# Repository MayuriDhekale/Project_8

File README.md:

# Project_8
<br>
<b><h2>Compact Li-Ion Charger & Microcontroller Board</h2></b>
<br>
Designed a custom circular 2-layer PCB to handle Li-Ion charging and audio alerts in a really compact form factor.

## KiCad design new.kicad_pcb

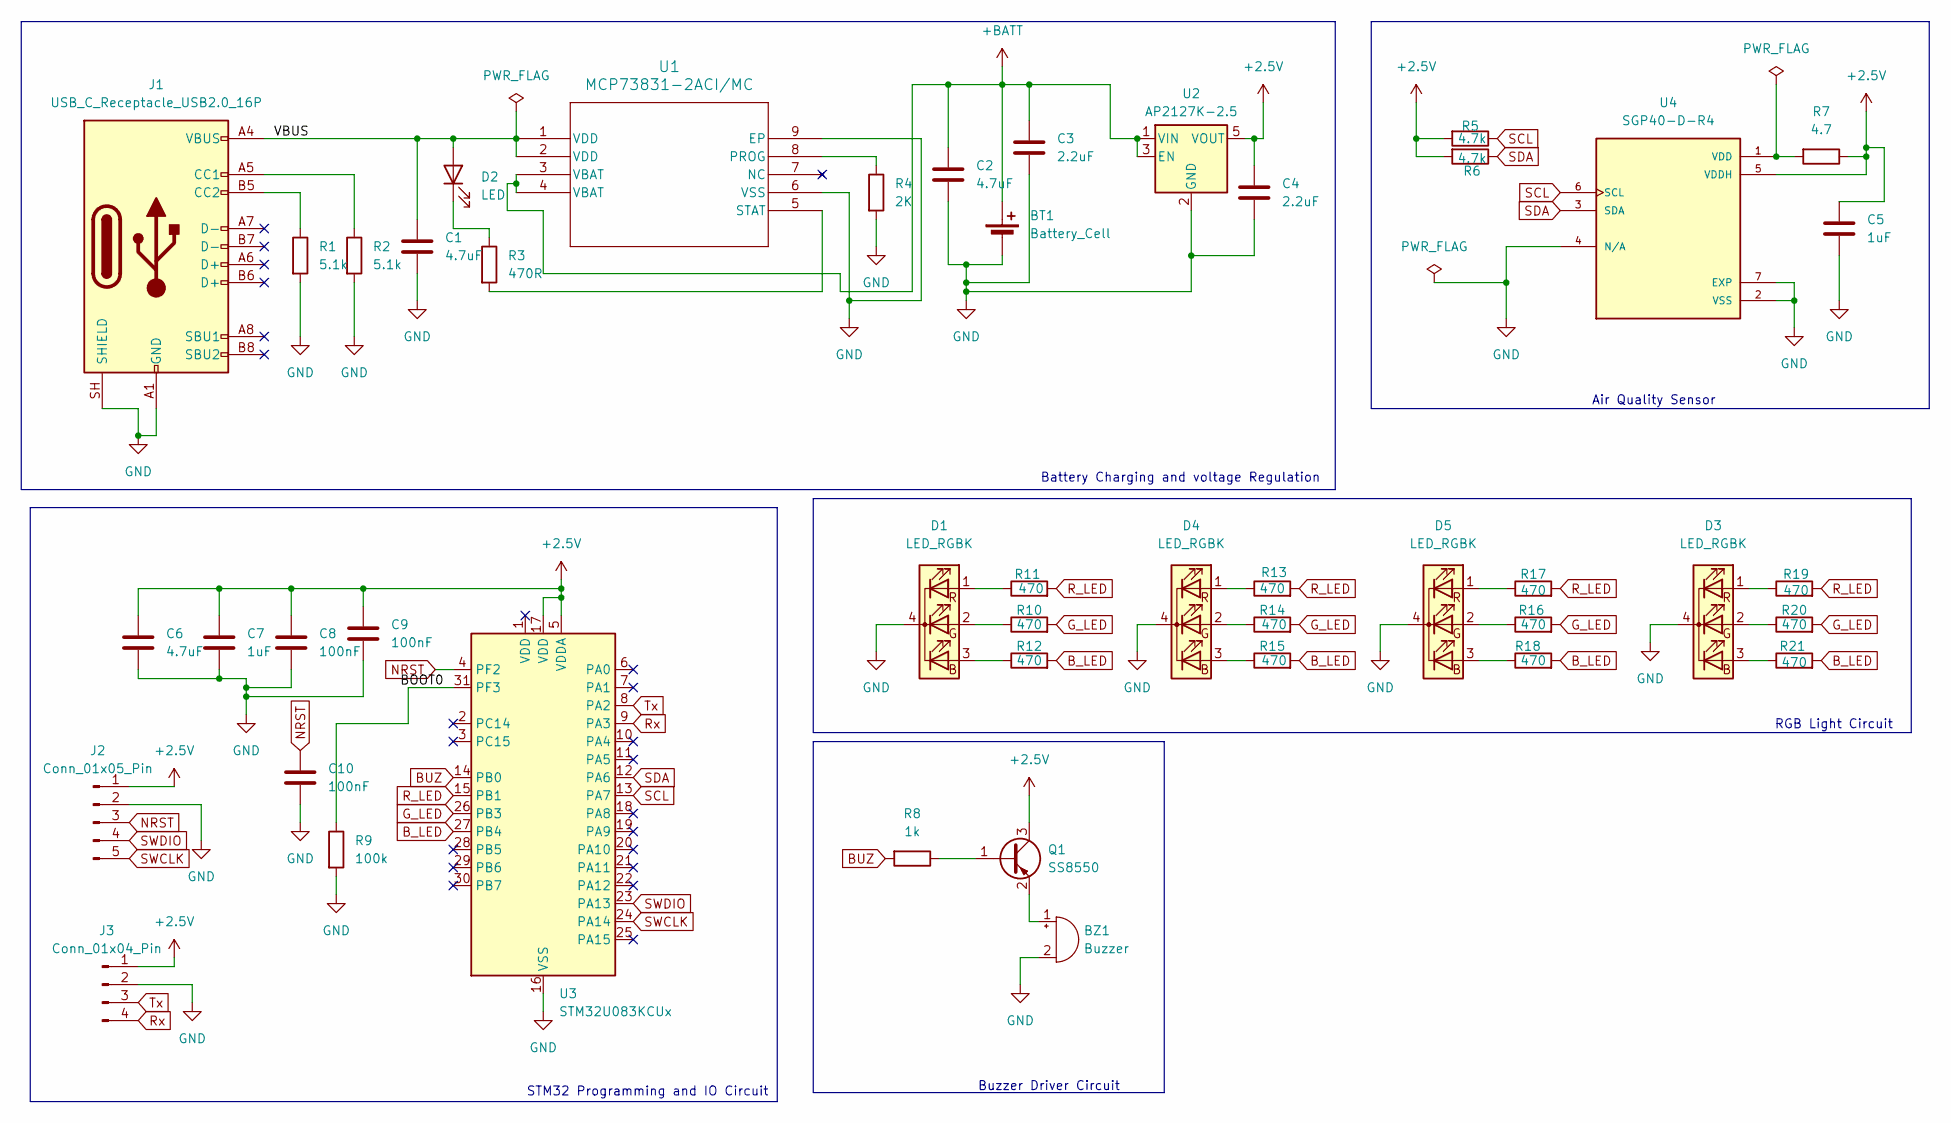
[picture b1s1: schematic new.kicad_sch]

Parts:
BT1: Battery_Cell; BatteryHolder_Keystone_3034_1x20mm
BZ1: Buzzer; Buzzer_Murata_PKMCS0909E
C1, C2, C6: 4.7uF; C_0603_1608Metric
C3, C4: 2.2uF; C_0603_1608Metric
C5, C7: 1uF; C_0603_1608Metric
C8, C9, C10: 100nF; C_0603_1608Metric
D1, D3, D4, D5: LED_RGBK; LED_RGB_1210
D2: LED; LED_0603_1608Metric
J1: USB_C_Receptacle_USB2.0_16P; USB_C_Receptacle_HRO_TYPE-C-31-M-12
J2: Conn_01x05_Pin; PinHeader_1x05_P2.54mm_Vertical
J3: Conn_01x04_Pin; PinHeader_1x04_P2.54mm_Vertical
Q1: SS8550; SOT-23
R1, R2: 5.1k; R_0603_1608Metric
R3: 470R; R_0603_1608Metric
R4: 2K; R_0603_1608Metric
R5, R6: 4.7k; R_0603_1608Metric
R7: 4.7; R_0603_1608Metric
R8: 1k; R_0603_1608Metric
R9: 100k; R_0603_1608Metric
R10, R11, R12, R13, R14, R15, R16, R17, R18, R19, R20, R21: 470; R_0603_1608Metric
U1: MCP73831-2ACI/MC; DFN-8-1EP_2x3mm_P0.5mm_EP0.61x2.2mm
U2: AP2127K-2.5; SOT-23-5
U3: STM32U083KCUx; QFN-32-1EP_5x5mm_P0.5mm_EP3.45x3.45mm
U4: SGP40-D-R4; XCDR_SGP40-D-R4; PARTREV 1.2; DigiKey_Part_Number 1649-SGP40-D-R4CT-ND

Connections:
+2.5V: C4.1, C5.1, C6.1, C7.1, C8.1, C9.1, J2.1, J3.1, Q1.3 (C), R5.2, R6.2, R7.1, U2.5 (VOUT), U3.5 (VDDA), U3.17 (VDD), U4.5 (VDDH)
+BATT: BT1.1 (+), C2.1, C3.1, U1.3 (VBAT), U1.4 (VBAT), U2.1 (VIN), U2.3 (EN)
/BOOT0: R9.1, U3.31 (PF3)
/VBUS: C1.1, D2.2 (A), J1.A4 (VBUS), J1.A9 (VBUS), J1.B4 (VBUS), J1.B9 (VBUS), U1.1 (VDD), U1.2 (VDD)
BUZ: R8.2, U3.14 (PB0)
B_LED: R12.2, R15.2, R18.2, R21.2, U3.27 (PB4)
GND: BT1.2 (-), BZ1.2 (-), C1.2, C2.2, C3.2, C4.2, C5.2, C6.2, C7.2, C8.2, C9.2, C10.2, D1.4 (K), D3.4 (K), D4.4 (K), D5.4 (K), J1.A1 (GND), J1.A12 (GND), J1.B1 (GND), J1.B12 (GND), J1.SH (SHIELD), J2.2, J3.2, R1.2, R2.2, R4.2, R9.2, U1.6 (VSS), U1.9 (EP), U2.2 (GND), U3.16 (VSS), U3.32 (VSS), U3.33 (VSS), U4.2 (VSS), U4.4 (N/A), U4.7 (EXP)
G_LED: R10.2, R14.2, R16.2, R20.2, U3.26 (PB3)
NRST: C10.1, J2.3, U3.4 (PF2)
unnamed: BZ1.1 (+), Q1.2 (E)
unnamed: D1.3 (BA), R12.1
unnamed: D1.2 (GA), R10.1
unnamed: D1.1 (RA), R11.1
unnamed: D2.1 (K), R3.1
unnamed: D3.3 (BA), R21.1
unnamed: D3.2 (GA), R20.1
unnamed: D3.1 (RA), R19.1
unnamed: D4.3 (BA), R15.1
unnamed: D4.2 (GA), R14.1
unnamed: D4.1 (RA), R13.1
unnamed: D5.3 (BA), R18.1
unnamed: D5.2 (GA), R16.1
unnamed: D5.1 (RA), R17.1
unnamed: J1.A5 (CC1), R2.1
unnamed: J1.B5 (CC2), R1.1
unnamed: Q1.1 (B), R8.1
unnamed: R4.1, U1.8 (PROG)
unnamed: R3.2, U1.5 (STAT)
unnamed: R7.2, U4.1 (VDD)
R_LED: R11.2, R13.2, R17.2, R19.2, U3.15 (PB1)
Rx: J3.4, U3.9 (PA3)
SCL: R5.1, U3.13 (PA7), U4.6 (SCL)
SDA: R6.1, U3.12 (PA6), U4.3 (SDA)
SWCLK: J2.5, U3.24 (PA14)
SWDIO: J2.4, U3.23 (PA13)
Tx: J3.3, U3.8 (PA2)

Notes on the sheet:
Battery Charging and voltage Regulation
STM32 Programming and IO Circuit
Air Quality Sensor
RGB Light Circuit
Buzzer Driver Circuit

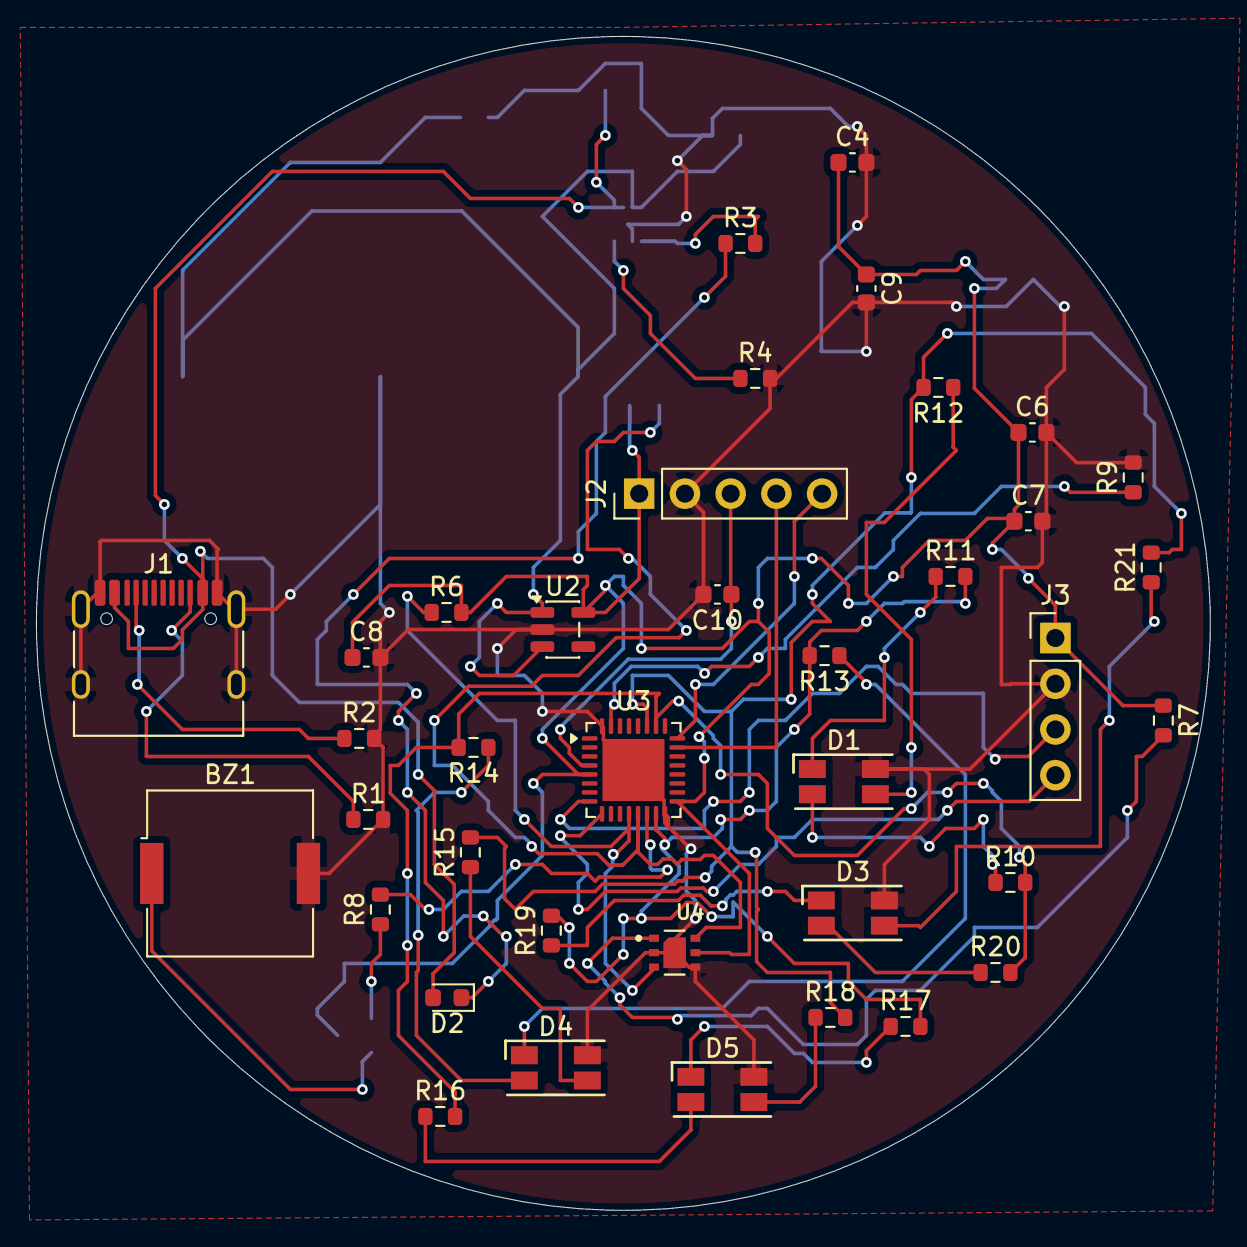
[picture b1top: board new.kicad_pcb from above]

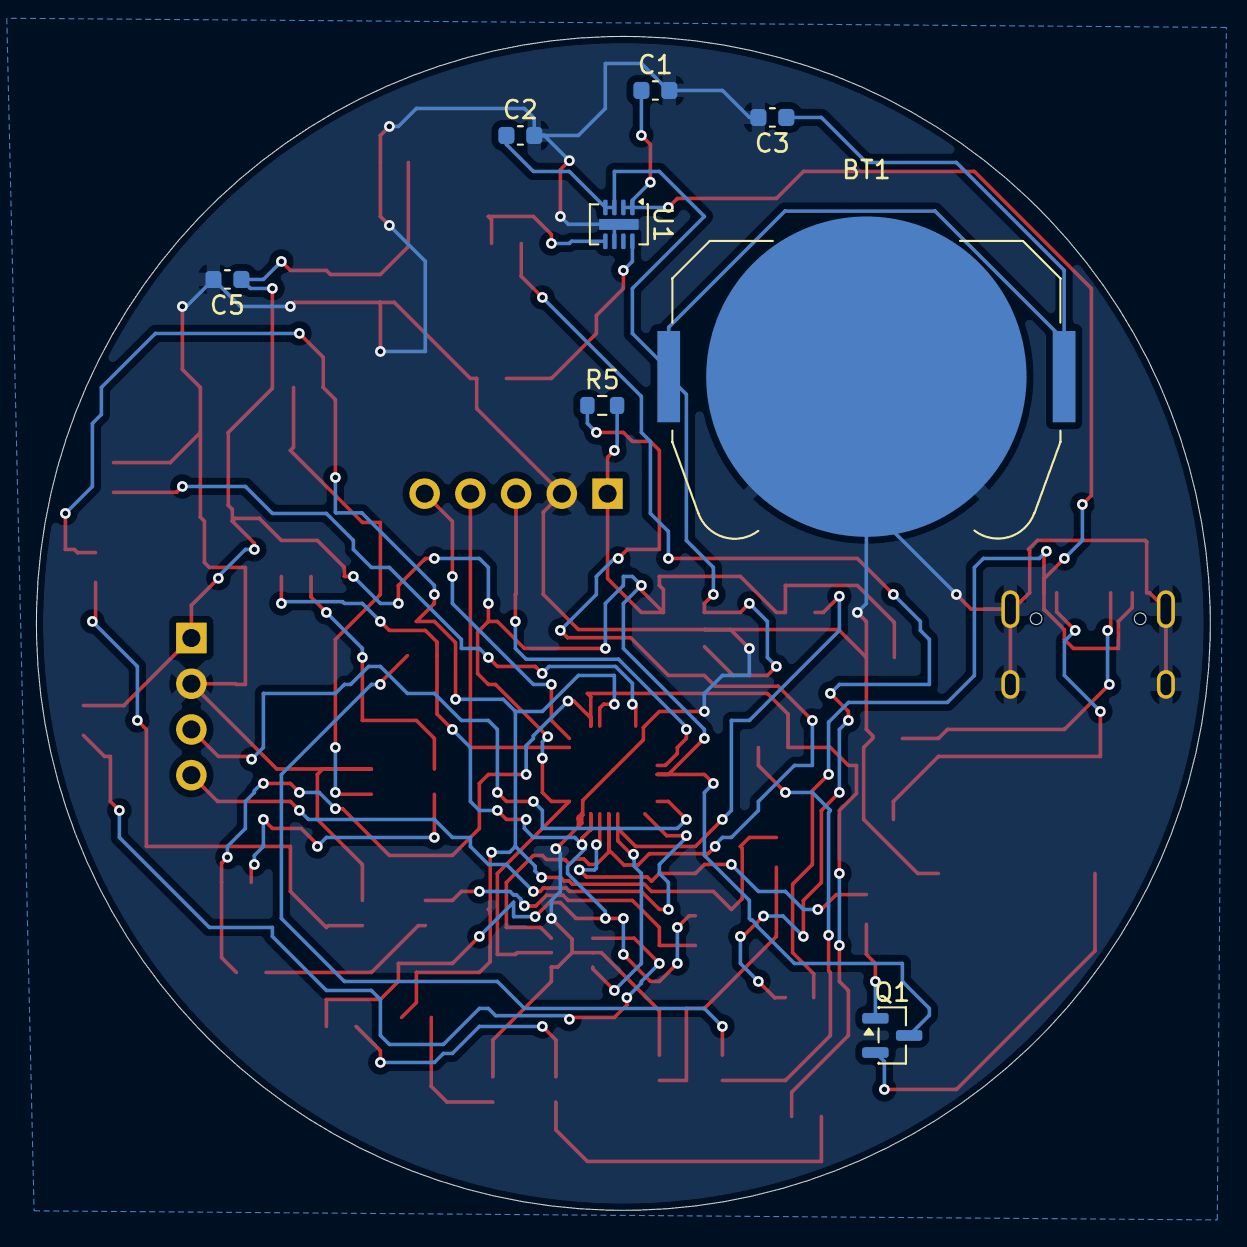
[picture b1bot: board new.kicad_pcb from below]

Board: 2 copper layers, 65.2 x 65.2 mm, 46 parts (8 on the bottom side), 36 nets.
